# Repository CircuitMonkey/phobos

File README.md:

# phobos
Doom Keycard inspired PCB, micro-edition with ATmega328P

I created a mini key card which is insprired by the Door Key Cards found in the original Doom game.

* Features
  * Measures 24.5mm long x 17.8mm high (1 inch x .7 inch).
  * Uses 0402 size parts for a good SMT soldering challenge.
  * Adding recommended components will allow it to run as an Arduino Uno clone (minus serial-usb).
  * All Arduino pins route to a pad.
  * Open Source!  Modify and embelish as desired.
  * Made with Eagle CAD

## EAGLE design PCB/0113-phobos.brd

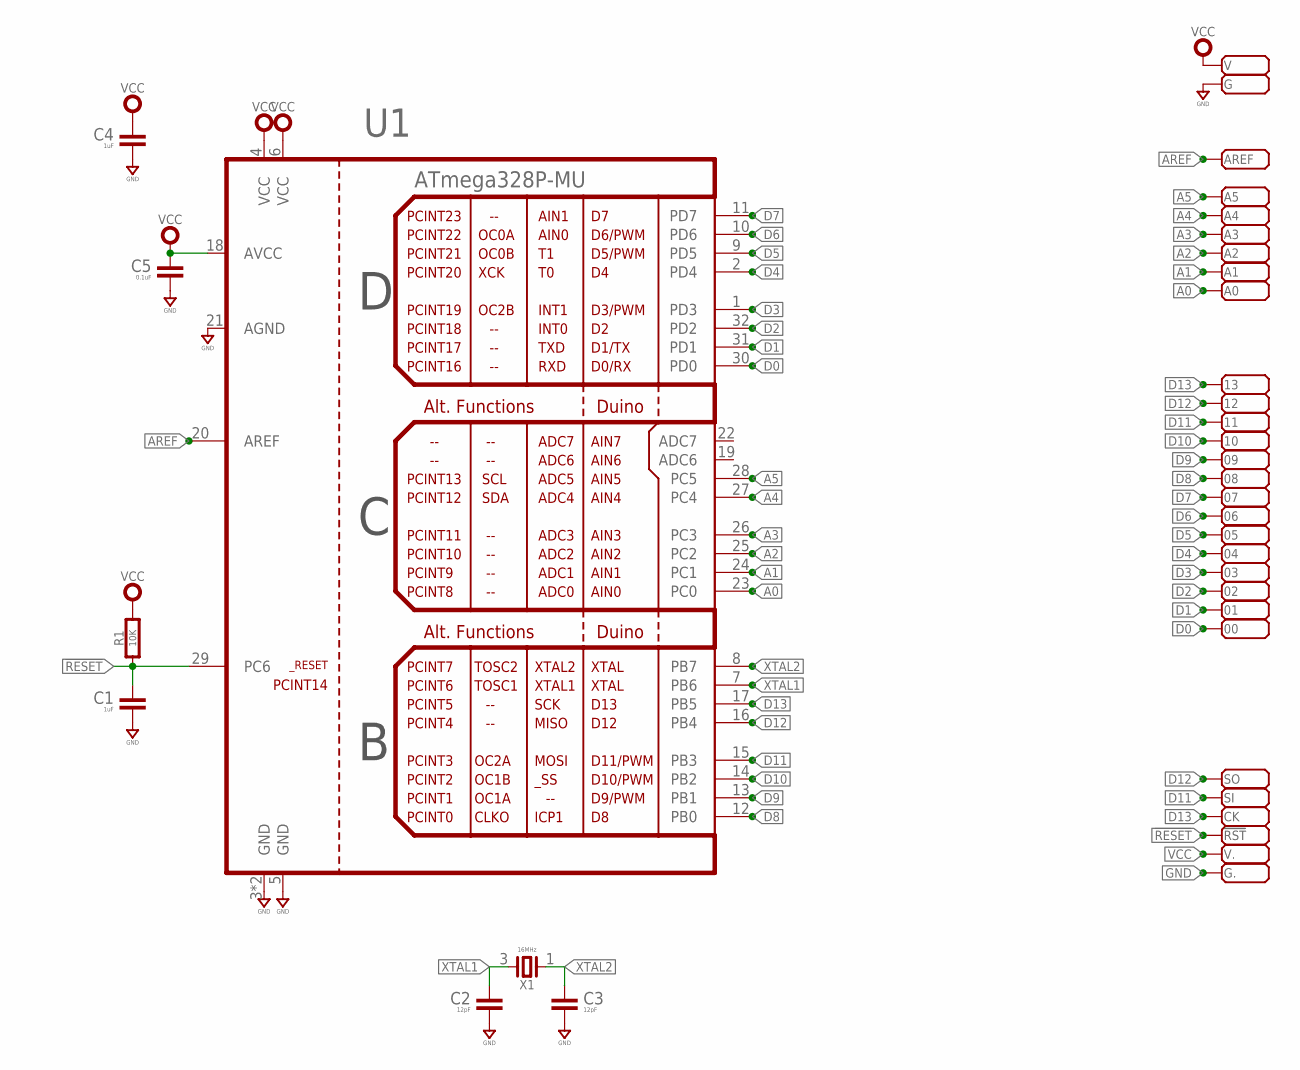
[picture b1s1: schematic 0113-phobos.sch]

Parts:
00, 01, 02, 03, 04, 05, 06, 07, 08, 09, 10, 11, 12, 13: PADSMD-070X070; SMD-070MIL
!RST: PADSMD-070X070; SMD-070MIL
A0, A1, A2, A3, A4, A5: PADSMD-070X070; SMD-070MIL
AREF: PADSMD-070X070; SMD-070MIL
C1, C4: 1uF; 0402-CAP
C2, C3: 12pF; 0402-CAP
C5: 0.1uF; 0402-CAP
CK: PADSMD-070X070; SMD-070MIL
G, G.: PADSMD-070X070; SMD-070MIL
R1: 10K; 0402-RES
SI: PADSMD-070X070; SMD-070MIL
SO: PADSMD-070X070; SMD-070MIL
U1: ATmega328P-MU; MLF32
V, V.: PADSMD-070X070; SMD-070MIL
X1: 16MHz; 32X25

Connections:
!RESET: !RST.1, C1.1, R1.1, U1.29 (PC6)
A0: A0.1, U1.23 (PC0)
A1: A1.1, U1.24 (PC1)
A2: A2.1, U1.25 (PC2)
A3: A3.1, U1.26 (PC3)
A4: A4.1, U1.27 (PC4)
A5: A5.1, U1.28 (PC5)
AREF: AREF.1, U1.20 (AREF)
D0: 00.1, U1.30 (PD0)
D1: 01.1, U1.31 (PD1)
D2: 02.1, U1.32 (PD2)
D3: 03.1, U1.1 (PD3)
D4: 04.1, U1.2 (PD4)
D5: 05.1, U1.9 (PD5)
D6: 06.1, U1.10 (PD6)
D7: 07.1, U1.11 (PD7)
D8: 08.1, U1.12 (PB0)
D9: 09.1, U1.13 (PB1)
D10: 10.1, U1.14 (PB2)
D11: 11.1, SI.1, U1.15 (PB3)
D12: 12.1, SO.1, U1.16 (PB4)
D13: 13.1, CK.1, U1.17 (PB5)
GND: C1.2, C2.2, C3.2, C4.2, C5.2, G.1, G..1, U1.3 (GND), U1.5 (GND), U1.21 (AGND), U1.PAD (GND)
VCC: C4.1, C5.1, R1.2, U1.4 (VCC), U1.6 (VCC), U1.18 (AVCC), V.1, V..1
XTAL1: C2.1, U1.7 (PB6), X1.3
XTAL2: C3.1, U1.8 (PB7), X1.1

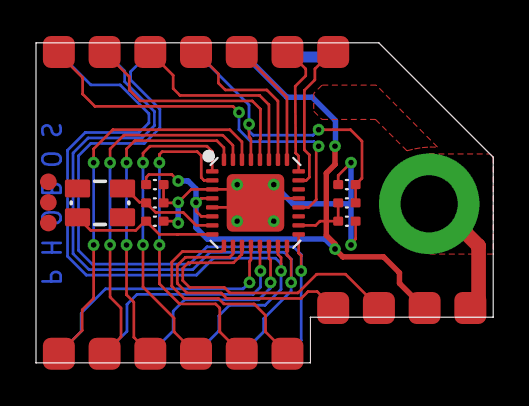
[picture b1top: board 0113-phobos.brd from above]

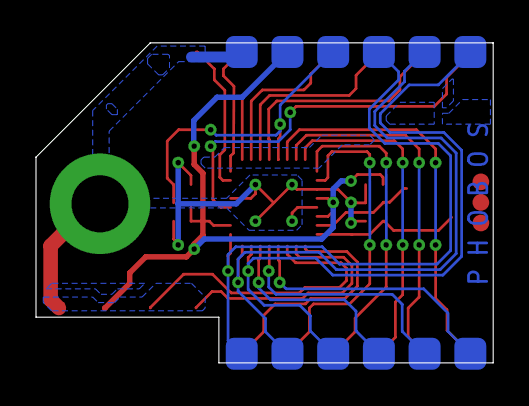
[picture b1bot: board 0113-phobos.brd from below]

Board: 2 copper layers, 25.4 x 17.8 mm, 37 parts (12 on the bottom side), 26 nets.

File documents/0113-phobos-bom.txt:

Partlist exported from /Users/mark/Workspaces-local/svn/CircuitMonkey/Products/Boards/0113-Phobos/PCB/phobos.sch at 1/5/20 8:36 PM

Part Value          Device         Package    Description    MF    MPN                 OC_MOUSER         OC_SEEED  VALUE        
!RST PADSMD-070X070 PADSMD-070X070 SMD-070MIL Solder Pad                                                                        
00   PADSMD-070X070 PADSMD-070X070 SMD-070MIL Solder Pad                                                                        
01   PADSMD-070X070 PADSMD-070X070 SMD-070MIL Solder Pad                                                                        
02   PADSMD-070X070 PADSMD-070X070 SMD-070MIL Solder Pad                                                                        
03   PADSMD-070X070 PADSMD-070X070 SMD-070MIL Solder Pad                                                                        
04   PADSMD-070X070 PADSMD-070X070 SMD-070MIL Solder Pad                                                                        
05   PADSMD-070X070 PADSMD-070X070 SMD-070MIL Solder Pad                                                                        
06   PADSMD-070X070 PADSMD-070X070 SMD-070MIL Solder Pad                                                                        
07   PADSMD-070X070 PADSMD-070X070 SMD-070MIL Solder Pad                                                                        
08   PADSMD-070X070 PADSMD-070X070 SMD-070MIL Solder Pad                                                                        
09   PADSMD-070X070 PADSMD-070X070 SMD-070MIL Solder Pad                                                                        
10   PADSMD-070X070 PADSMD-070X070 SMD-070MIL Solder Pad                                                                        
11   PADSMD-070X070 PADSMD-070X070 SMD-070MIL Solder Pad                                                                        
12   PADSMD-070X070 PADSMD-070X070 SMD-070MIL Solder Pad                                                                        
13   PADSMD-070X070 PADSMD-070X070 SMD-070MIL Solder Pad                                                                        
A0   PADSMD-070X070 PADSMD-070X070 SMD-070MIL Solder Pad                                                                        
A1   PADSMD-070X070 PADSMD-070X070 SMD-070MIL Solder Pad                                                                        
A2   PADSMD-070X070 PADSMD-070X070 SMD-070MIL Solder Pad                                                                        
A3   PADSMD-070X070 PADSMD-070X070 SMD-070MIL Solder Pad                                                                        
A4   PADSMD-070X070 PADSMD-070X070 SMD-070MIL Solder Pad                                                                        
A5   PADSMD-070X070 PADSMD-070X070 SMD-070MIL Solder Pad                                                                        
AREF PADSMD-070X070 PADSMD-070X070 SMD-070MIL Solder Pad                                                                        
C1   1uF            CAPACITOR0402  0402-CAP   Capacitor  CAP                                                                    
C2   12pF           CAPACITOR0402  0402-CAP   Capacitor  CAP                                                                    
C3   12pF           CAPACITOR0402  0402-CAP   Capacitor  CAP                                                                    
C4   1uF            CAPACITOR0402  0402-CAP   Capacitor  CAP                                                                    
C5   0.1uF          CAPACITOR0402  0402-CAP   Capacitor  CAP                                                                    
CK   PADSMD-070X070 PADSMD-070X070 SMD-070MIL Solder Pad                                                                        
G    PADSMD-070X070 PADSMD-070X070 SMD-070MIL Solder Pad                                                                        
G.   PADSMD-070X070 PADSMD-070X070 SMD-070MIL Solder Pad                                                                        
R1   10K            RESISTOR0402   0402-RES   Resistor                                                                          
SI   PADSMD-070X070 PADSMD-070X070 SMD-070MIL Solder Pad                                                                        
SO   PADSMD-070X070 PADSMD-070X070 SMD-070MIL Solder Pad                                                                        
U1   ATmega328P-MU  ATMEGA328MU    MLF32      Atmega 328P    Atmel atmega328p-mu       556-ATMEGA328P-MU 310010005 ATmega328P-MU
V    PADSMD-070X070 PADSMD-070X070 SMD-070MIL Solder Pad                                                                        
V.   PADSMD-070X070 PADSMD-070X070 SMD-070MIL Solder Pad                                                                        
X1   16MHz          2P3.2X2.5      32X25      Crystal        Epson FA-238 16.0000MB-K3                             16MHz

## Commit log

2020-01-06 Add Phobos Rev.A to Github
